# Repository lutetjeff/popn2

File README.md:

# popn2 (lutet)

version 2 of my personal pop'n music controller! we don't talk about version 1.

here is me clearing my first 44 on this controller: [video link](https://github.com/user-attachments/assets/4b452afc-de7f-416d-95ad-3e25626bb59a)

## Repository Hierarchy

- **`daughterboard/`**: KiCAD PCB files for the USB and power daughterboard.
- **`firmware/`**: Source code for the mainboard's firmware.
- **`mainboard/`**: KiCAD PCB files for the STM32F072 mainboard.
- **`media/`**: Images, renders, and video showcases of the controller.
- **`production/`**: Vector files for laser-cutting the physical enclosure layers.
- **`popn2.f3z`**: Fusion 360 source file for the mechanical design.

## Mechanical Design

The physical enclosure of the controller is built using a stacked layer design. The stackup consists of:
- **13 layers of birch plywood** (Layers 1 through 13). The nominal thickness is 1/4", but the actual real-world thickness is about **5.2mm** per layer.
- **1 layer of acetal/POM** measuring **3/8" (9.5mm)** thick for the top layer.

### Buttons & Hardware
- **Gameplay Buttons:** We use 100mm Samducksa buttons from ISTMALL for the 9 main gameplay buttons. We highly recommend getting the aftermarket 100g Samducksa springs from ISTMALL rather than using the stock springs.
- **Side Buttons (Pop-kuns):** The side buttons are these 60mm OEM round buttons: [Amazon Link](https://www.amazon.com/dp/B09CYMDZCR)

## Mainboard

The mainboard is powered by an **STM32F072** microcontroller, and also functions as a generic 12-input 12-output arcade game controller. It uses individual pins for each button and darlington arrays to drive 12V LEDs.

## Daughterboard

The daughterboard handles the external inputs for the controller. The KiCAD PCB files define a board that takes **12V and USB in** and passes them along to the mainboard via a **10-pin (2x5) ribbon cable**.

## Firmware

The firmware for the STM32F072 on the mainboard is included in this repository.
For more details, please see the [firmware README](firmware/README.md).

## Production

The `production/` folder contains the production files for laser cutting each individual layer. 
The naming convention for these files is `sl[layer][part]`, where `[part]` is at most one digit.
There are also combined production files in `production/combined/` - beware that one of the pieces is missing and I don't remember which one. 

## Special Thanks

- **Illini Rhythm Syndicate** ([link](https://uiucirs.com))
- **ECE OpenLab at UIUC** ([link](https://openlab.ece.illinois.edu/))

## As Seen At

- Rumble In The Prairie 15 (RIP 15) - [link](https://www.start.gg/tournament/rumble-in-the-prairie-15/details)
- IRSCTF 2026 - [link](https://ctf.uiucirs.com/)
- This controller is so awesome [they made a whole song about it](https://www.youtube.com/watch?v=c7E-tgmFuzw)

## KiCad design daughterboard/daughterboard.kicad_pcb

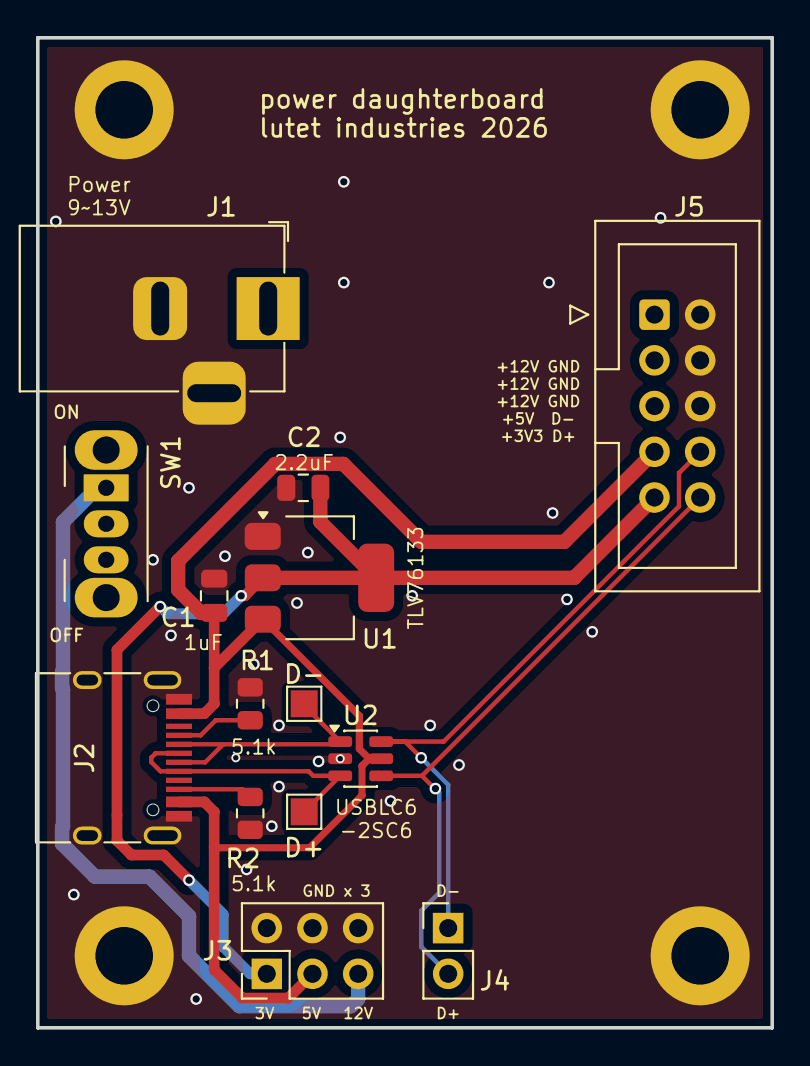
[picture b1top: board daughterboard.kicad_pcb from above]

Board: 2 copper layers, 40.8 x 55.0 mm, 18 parts (0 on the bottom side), 11 nets.

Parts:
C1: 1uF; C_0805_2012Metric
C2: 2.2uF; C_0805_2012Metric
D+: D+; TestPoint_Pad_1.5x1.5mm
D-: D-; TestPoint_Pad_1.5x1.5mm
H1, H2, H3, H4: MountingHole_Pad; MountingHole_3.2mm_M3_ISO14580_Pad
J1: Barrel_Jack_MountingPin; BarrelJack_Horizontal
J2: USB_C_Receptacle_USB2.0_16P; USB_C_Receptacle_HRO_TYPE-C-31-M-12
J3: PWR; PinHeader_2x03_P2.54mm_Vertical
J4: DATA; PinHeader_1x02_P2.54mm_Vertical
J5: ribbon; IDC-Header_2x05_P2.54mm_Vertical
R1, R2: 5.1k; R_0805_2012Metric
SW1: SW_SPDT; SW_Slide_SPDT_Angled_CK_OS102011MA1Q
U1: TLV76133DCY; SOT-223-3_TabPin2
U2: USBLC6-2SC6; SOT-23-6

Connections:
+3V3: C2.1, J3.1, J5.9, U1.2 (VO)
+5V: C1.1, J2.A4 (VBUS), J2.A9 (VBUS), J2.B4 (VBUS), J2.B9 (VBUS), J3.3, J5.7, U1.3 (VI), U2.5 (VBUS)
+12V: J3.5, J5.1, J5.3, J5.5, SW1.1 (A)
D+: J4.2, J5.10, U2.4 (I/O2)
D-: J4.1, J5.8, U2.6 (I/O1)
GND: C1.2, C2.2, H1.1, H2.1, H3.1, H4.1, J1.2, J1.3 (MountPin), J2.A1 (GND), J2.A12 (GND), J2.B1 (GND), J2.B12 (GND), J2.S1 (SHIELD), J3.2, J3.4, J3.6, J5.2, J5.4, J5.6, R1.2, R2.2, U1.1 (GND), U2.2 (GND)
unnamed: J2.A5 (CC1), R1.1
unnamed: J2.B5 (CC2), R2.1
unnamed: D+.1, J2.A6 (D+), J2.B6 (D+), U2.3 (I/O2)
unnamed: D-.1, J2.A7 (D-), J2.B7 (D-), U2.1 (I/O1)
unnamed: J1.1, SW1.2 (B)

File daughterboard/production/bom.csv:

Designator,Footprint,Quantity,Value,LCSC Part #
C1,0805,1,1uF,
C2,0805,1,2.2uF,
D+,TestPoint_Pad_1.5x1.5mm,1,D+,
D-,TestPoint_Pad_1.5x1.5mm,1,D-,
J1,BarrelJack_Horizontal,1,Barrel_Jack_MountingPin,
J2,USB_C_Receptacle_HRO_TYPE-C-31-M-12,1,USB_C_Receptacle_USB2.0_16P,
J3,PinHeader_2x03_P2.54mm_Vertical,1,PWR,
J4,PinHeader_1x02_P2.54mm_Vertical,1,DATA,
J5,IDC-Header_2x05_P2.54mm_Vertical,1,ribbon,
"R1, R2",0805,2,5.1k,
SW1,SW_Slide_SPDT_Angled_CK_OS102011MA1Q,1,SW_SPDT,
U1,SOT-223-3_TabPin2,1,TLV76133DCY,
U2,SOT-23-6,1,USBLC6-2SC6,

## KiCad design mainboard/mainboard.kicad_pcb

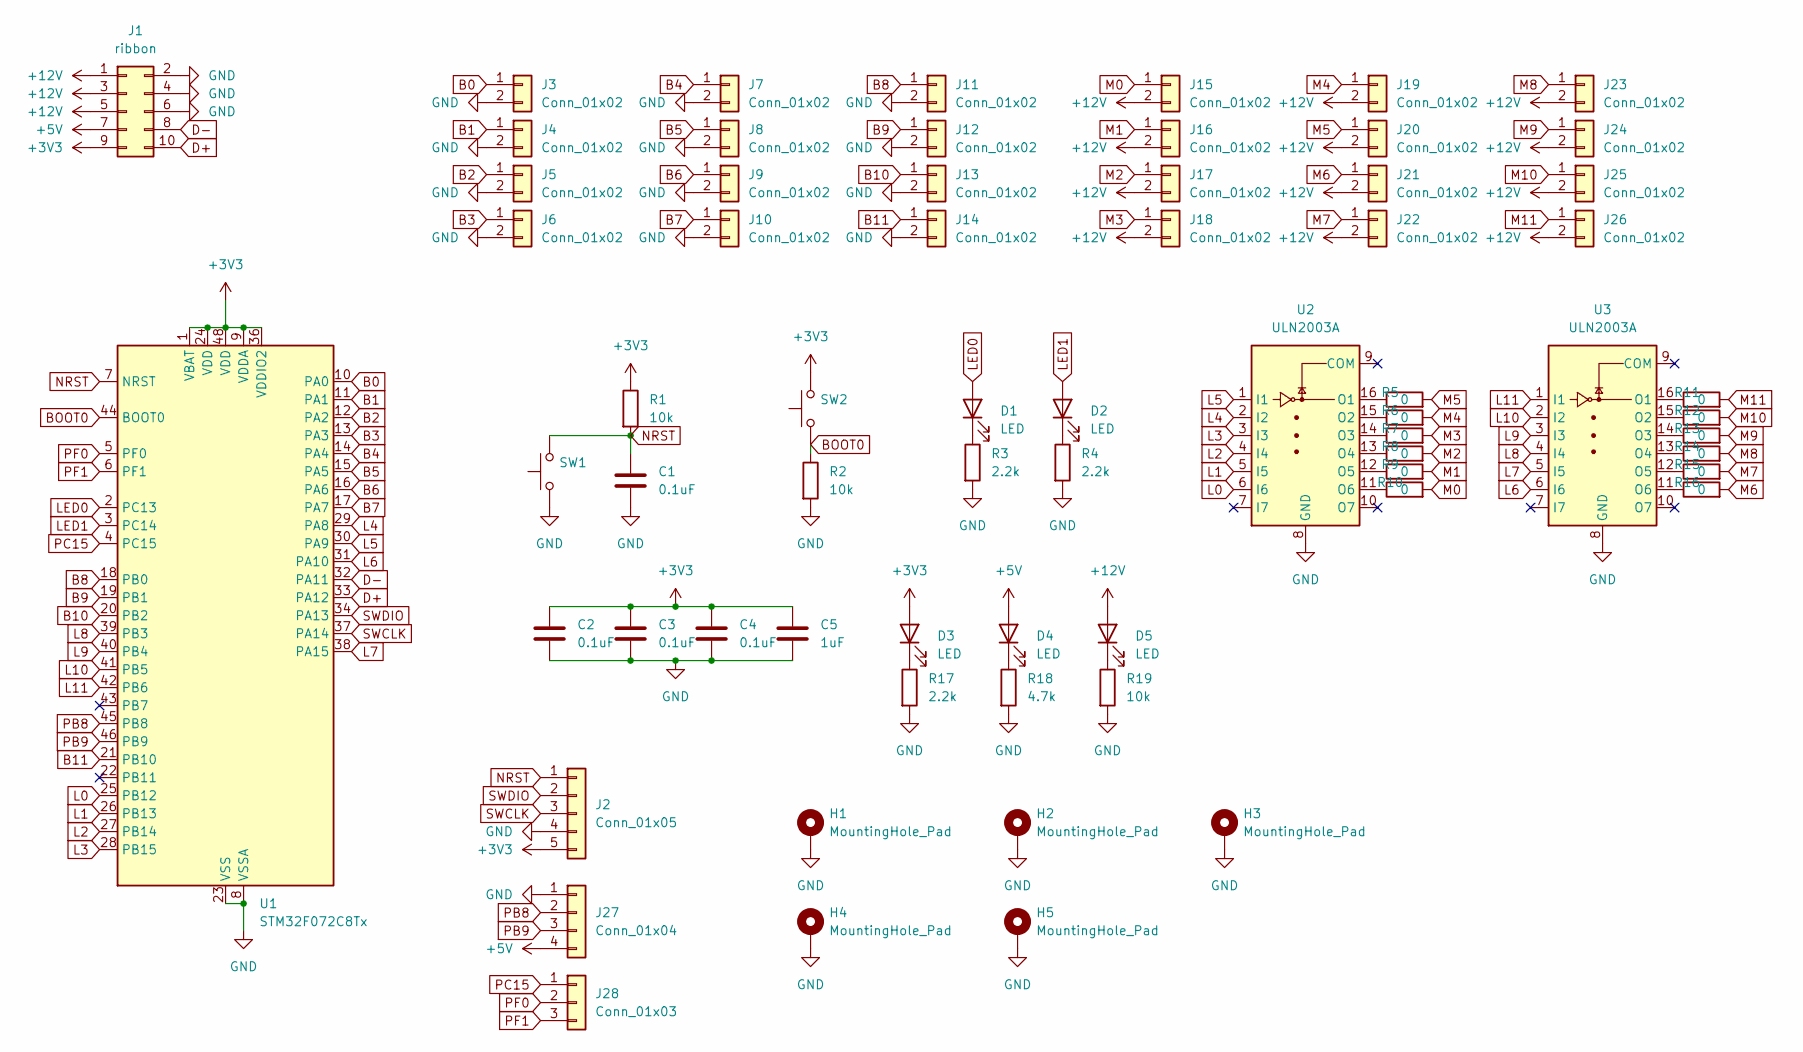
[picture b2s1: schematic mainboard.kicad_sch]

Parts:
C1, C2, C3, C4: 0.1uF; C_0805_2012Metric
C5: 1uF; C_0805_2012Metric
D1, D2, D3, D4, D5: LED; LED_0805_2012Metric
H1, H2, H3, H4, H5: MountingHole_Pad; MountingHole_3.2mm_M3_ISO14580_Pad
J1: ribbon; IDC-Header_2x05_P2.54mm_Vertical
J2: Conn_01x05; PinSocket_1x05_P2.54mm_Vertical
J3, J4, J5, J6, J7, J8, J9, J10, J11, J12, J13, J14, J15, J16, J17, J18, J19, J20, J21, J22, J23, J24, J25, J26: Conn_01x02; TerminalBlock_MaiXu_MX126-5.0-02P_1x02_P5.00mm
J27: Conn_01x04; PinHeader_1x04_P2.54mm_Vertical
J28: Conn_01x03; PinHeader_1x03_P2.54mm_Vertical
R1, R2, R19: 10k; R_0805_2012Metric
R3, R4, R17: 2.2k; R_0805_2012Metric
R5, R6, R7, R8, R9, R10, R11, R12, R13, R14, R15, R16: 0; R_0805_2012Metric
R18: 4.7k; R_0805_2012Metric
SW1, SW2: SW_Push; SW_SPST_PTS810
U1: STM32F072C8Tx; LQFP-48_7x7mm_P0.5mm
U2, U3: ULN2003A; SOIC-16_3.9x9.9mm_P1.27mm

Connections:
+3V3: C2.1, C3.1, C4.1, C5.1, D3.2 (A), J1.9, J2.5, R1.1, SW2.2, U1.1 (VBAT), U1.9 (VDDA), U1.24 (VDD), U1.36 (VDDIO2), U1.48 (VDD)
+5V: D4.2 (A), J1.7, J27.4
+12V: D5.2 (A), J1.1, J1.3, J1.5, J15.2, J16.2, J17.2, J18.2, J19.2, J20.2, J21.2, J22.2, J23.2, J24.2, J25.2, J26.2
B0: J3.1, U1.10 (PA0)
B1: J4.1, U1.11 (PA1)
B2: J5.1, U1.12 (PA2)
B3: J6.1, U1.13 (PA3)
B4: J7.1, U1.14 (PA4)
B5: J8.1, U1.15 (PA5)
B6: J9.1, U1.16 (PA6)
B7: J10.1, U1.17 (PA7)
B8: J11.1, U1.18 (PB0)
B9: J12.1, U1.19 (PB1)
B10: J13.1, U1.20 (PB2)
B11: J14.1, U1.21 (PB10)
BOOT0: R2.1, SW2.1, U1.44 (BOOT0)
D+: J1.10, U1.33 (PA12)
D-: J1.8, U1.32 (PA11)
GND: C1.2, C2.2, C3.2, C4.2, C5.2, H1.1, H2.1, H3.1, H4.1, H5.1, J1.2, J1.4, J1.6, J2.4, J3.2, J4.2, J5.2, J6.2, J7.2, J8.2, J9.2, J10.2, J11.2, J12.2, J13.2, J14.2, J27.1, R2.2, R3.2, R4.2, R17.2, R18.2, R19.2, SW1.1, U1.8 (VSSA), U1.23 (VSS), U1.35 (VSS), U1.47 (VSS), U2.8 (GND), U3.8 (GND)
L0: U1.25 (PB12), U2.6 (I6)
L1: U1.26 (PB13), U2.5 (I5)
L2: U1.27 (PB14), U2.4 (I4)
L3: U1.28 (PB15), U2.3 (I3)
L4: U1.29 (PA8), U2.2 (I2)
L5: U1.30 (PA9), U2.1 (I1)
L6: U1.31 (PA10), U3.6 (I6)
L7: U1.38 (PA15), U3.5 (I5)
L8: U1.39 (PB3), U3.4 (I4)
L9: U1.40 (PB4), U3.3 (I3)
L10: U1.41 (PB5), U3.2 (I2)
L11: U1.42 (PB6), U3.1 (I1)
LED0: D1.2 (A), U1.2 (PC13)
LED1: D2.2 (A), U1.3 (PC14)
M0: J15.1, R10.2
M1: J16.1, R9.2
M2: J17.1, R8.2
M3: J18.1, R7.2
M4: J19.1, R6.2
M5: J20.1, R5.2
M6: J21.1, R16.2
M7: J22.1, R15.2
M8: J23.1, R14.2
M9: J24.1, R13.2
M10: J25.1, R12.2
M11: J26.1, R11.2
NRST: C1.1, J2.1, R1.2, SW1.2, U1.7 (NRST)
unnamed: D1.1 (K), R3.1
unnamed: D2.1 (K), R4.1
unnamed: D3.1 (K), R17.1
unnamed: D4.1 (K), R18.1
unnamed: D5.1 (K), R19.1
unnamed: R5.1, U2.16 (O1)
unnamed: R6.1, U2.15 (O2)
unnamed: R7.1, U2.14 (O3)
unnamed: R8.1, U2.13 (O4)
unnamed: R9.1, U2.12 (O5)
unnamed: R10.1, U2.11 (O6)
unnamed: R11.1, U3.16 (O1)
unnamed: R12.1, U3.15 (O2)
unnamed: R13.1, U3.14 (O3)
unnamed: R14.1, U3.13 (O4)
unnamed: R15.1, U3.12 (O5)
unnamed: R16.1, U3.11 (O6)
PB8: J27.2, U1.45 (PB8)
PB9: J27.3, U1.46 (PB9)
PC15: J28.1, U1.4 (PC15)
PF0: J28.2, U1.5 (PF0)
PF1: J28.3, U1.6 (PF1)
SWCLK: J2.3, U1.37 (PA14)
SWDIO: J2.2, U1.34 (PA13)

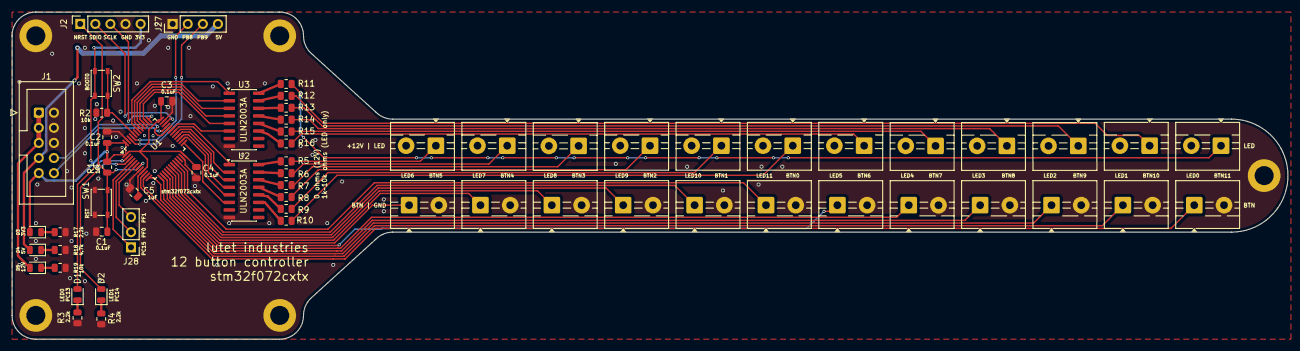
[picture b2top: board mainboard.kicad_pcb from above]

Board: 2 copper layers, 214.5 x 55.0 mm, 67 parts (0 on the bottom side), 70 nets.

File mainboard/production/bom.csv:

Designator,Footprint,Quantity,Value,LCSC Part #
"C1, C2, C3, C4",0805,4,0.1uF,
C5,0805,1,1uF,
"D1, D2, D3, D4, D5",0805,5,LED,
J1,IDC-Header_2x05_P2.54mm_Vertical,1,ribbon,
"J10, J11, J12, J13, J14, J15, J16, J17, J18, J19, J20, J21, J22, J23, J24, J25, J26, J3, J4, J5, J6, J7, J8, J9",TerminalBlock_MaiXu_MX126-5.0-02P_1x02_P5.00mm,24,Conn_01x02,
J2,PinSocket_1x05_P2.54mm_Vertical,1,Conn_01x05,
J27,PinHeader_1x04_P2.54mm_Vertical,1,Conn_01x04,
J28,PinHeader_1x03_P2.54mm_Vertical,1,Conn_01x03,
"R1, R19, R2",0805,3,10k,
"R10, R11, R12, R13, R14, R15, R16, R5, R6, R7, R8, R9",0805,12,0,
"R17, R3, R4",0805,3,2.2k,
R18,0805,1,4.7k,
"SW1, SW2",SW_SPST_PTS810,2,SW_Push,
U1,LQFP-48_7x7mm_P0.5mm,1,STM32F072C8Tx,
"U2, U3",SOIC-16_3.9x9.9mm_P1.27mm,2,ULN2003A,

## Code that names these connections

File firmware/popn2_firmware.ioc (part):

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Mcu.Name=STM32F072C(8-B)Tx
Mcu.Package=LQFP48
Mcu.UserName=STM32F072CBTx
PA0.GPIOParameters=GPIO_PuPd,GPIO_Label
PA0.GPIO_Label=B0
PA0.GPIO_PuPd=GPIO_PULLUP
PA0.Signal=GPIO_Input
PA1.GPIOParameters=GPIO_PuPd,GPIO_Label
PA1.GPIO_Label=B1
PA1.GPIO_PuPd=GPIO_PULLUP
PA1.Signal=GPIO_Input
PA10.GPIOParameters=GPIO_Label
PA10.GPIO_Label=L6
PA10.Signal=GPIO_Output
PA11.Mode=Device
PA11.Signal=USB_DM
PA12.Mode=Device
PA12.Signal=USB_DP
PA15.GPIOParameters=GPIO_Label
PA15.GPIO_Label=L7
PA15.Signal=GPIO_Output
PA2.GPIOParameters=GPIO_PuPd,GPIO_Label
PA2.GPIO_Label=B2
PA2.GPIO_PuPd=GPIO_PULLUP
PA2.Signal=GPIO_Input
PA3.GPIOParameters=GPIO_PuPd,GPIO_Label
PA3.GPIO_Label=B3
PA3.GPIO_PuPd=GPIO_PULLUP
PA3.Signal=GPIO_Input
PA4.GPIOParameters=GPIO_PuPd,GPIO_Label
PA4.GPIO_Label=B4
PA4.GPIO_PuPd=GPIO_PULLUP
PA4.Signal=GPIO_Input
PA5.GPIOParameters=GPIO_PuPd,GPIO_Label
PA5.GPIO_Label=B5
PA5.GPIO_PuPd=GPIO_PULLUP
PA5.Signal=GPIO_Input
PA6.GPIOParameters=GPIO_PuPd,GPIO_Label
PA6.GPIO_Label=B6
PA6.GPIO_PuPd=GPIO_PULLUP
PA6.Signal=GPIO_Input
PA7.GPIOParameters=GPIO_PuPd,GPIO_Label
PA7.GPIO_Label=B7
PA7.GPIO_PuPd=GPIO_PULLUP
PA7.Signal=GPIO_Input
PA8.GPIOParameters=GPIO_Label
PA8.GPIO_Label=L4
PA8.Signal=GPIO_Output
PA9.GPIOParameters=GPIO_Label
PA9.GPIO_Label=L5
PA9.Signal=GPIO_Output
PB0.GPIOParameters=GPIO_PuPd,GPIO_Label
PB0.GPIO_Label=B8
PB0.GPIO_PuPd=GPIO_PULLUP
PB0.Signal=GPIO_Input
PB1.GPIOParameters=GPIO_PuPd,GPIO_Label
PB1.GPIO_Label=B9
PB1.GPIO_PuPd=GPIO_PULLUP
PB1.Signal=GPIO_Input
PB10.GPIOParameters=GPIO_PuPd,GPIO_Label
PB10.GPIO_Label=B11
PB10.GPIO_PuPd=GPIO_PULLUP
PB10.Signal=GPIO_Input
PB12.GPIOParameters=GPIO_Label
PB12.GPIO_Label=L0
PB12.Signal=GPIO_Output
PB13.GPIOParameters=GPIO_Label
PB13.GPIO_Label=L1
PB13.Signal=GPIO_Output
PB14.GPIOParameters=GPIO_Label
PB14.GPIO_Label=L2
PB14.Signal=GPIO_Output
PB15.GPIOParameters=GPIO_Label
PB15.GPIO_Label=L3
PB15.Signal=GPIO_Output
PB2.GPIOParameters=GPIO_PuPd,GPIO_Label
PB2.GPIO_Label=B10
PB2.GPIO_PuPd=GPIO_PULLUP
PB2.Signal=GPIO_Input
PB3.GPIOParameters=GPIO_Label
PB3.GPIO_Label=L8
PB3.Signal=GPIO_Output
PB4.GPIOParameters=GPIO_Label
PB4.GPIO_Label=L9
PB4.Signal=GPIO_Output
PB5.GPIOParameters=GPIO_Label
PB5.GPIO_Label=L10
PB5.Signal=GPIO_Output
PB6.GPIOParameters=GPIO_Label
PB6.GPIO_Label=L11
PB6.Signal=GPIO_Output
PB8.Signal=I2C1_SCL
PB9.Signal=I2C1_SDA
PC13.GPIOParameters=GPIO_Label
PC13.GPIO_Label=LED0
PC13.Signal=GPIO_Output
PC14-OSC32_IN.GPIOParameters=GPIO_Label
PC14-OSC32_IN.GPIO_Label=LED1
PC14-OSC32_IN.Signal=GPIO_Output
RCC.SYSCLKFreq_VALUE=48000000
RCC.SYSCLKSource=RCC_SYSCLKSOURCE_HSI48
board=custom

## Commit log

2026-04-07 PCBs, production files
2026-04-07 add .gitignore
2026-04-07 firmware
2026-04-07 add media
2026-04-07 add render
2026-04-07 readme
2026-04-07 readme: add as seen at section
    add as seen at section with obligatory "pop in 2" joke
2026-04-07 readme: upload video nicer
